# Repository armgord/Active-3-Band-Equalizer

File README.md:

# Electronic Circuit Design & Characterization Portfolio

[cite_start]A collection of high-performance analog and power electronics projects developed at **Tecnológico de Monterrey**[cite: 610, 612]. This repository documents the design, simulation, and physical implementation of fundamental electronic systems.

## 🚀 Projects Overview

### 1. Instrumentation Amplifier & Signal Conditioning
[cite_start]Designed a high-precision instrumentation amplifier using the **TL084 OpAmp**[cite: 787, 798]. 
* [cite_start]**Key Feature:** Achieved effective rejection of a 1V common-mode offset, outputting only the amplified differential signal[cite: 782, 783, 844].
* [cite_start]**Applications:** Sensor data acquisition and small-signal conditioning[cite: 783, 863].

### 2. Audio Power Amplifier (Push-Pull)
[cite_start]Developed a "Mono" audio amplifier combining an inverting OpAmp stage for gain control with a **TIP41C/TIP42C complementary push-pull stage**[cite: 978, 1012].
* [cite_start]**Performance:** Capable of driving an 8Ω speaker with high current (up to 6A) and minimal harmonic distortion[cite: 980, 1013, 1065].

### 3. Adjustable Voltage Regulator (1V - 12V)
[cite_start]Implemented a series linear regulator using an **LM358 OpAmp**, a Zener diode reference, and a **TIP31C power transistor**[cite: 869, 873].
* [cite_start]**Specs:** Adjustable output from 0.1V up to 12.3V with high-current stability (up to 300mA)[cite: 873, 943, 949, 957].

### 4. Signal Generation & PWM Motor Control
* [cite_start]**Waveform Generator:** Designed an oscillator for simultaneous square and triangular wave generation[cite: 1069, 1074].
* [cite_start]**DC Motor Control:** Implemented a speed control system using an **NE555 timer** for Pulse Width Modulation (PWM) to drive a DC motor via a chopper converter[cite: 1132, 1133, 1146].

## 📊 Characterization & Analysis
Each project includes detailed mathematical modeling and experimental verification:
* [cite_start]**Frequency Analysis:** Bode plots for Integrator/Differentiator circuits[cite: 752, 774].
* [cite_start]**Thermal Modeling:** Calculated heat sink requirements ($R_{\theta}$ ≈ 22.83°C/W) for power transistors[cite: 1017].
* [cite_start]**Efficiency:** Evaluation of power dissipation and conversion efficiency in linear vs. switching topologies[cite: 935, 936].

## 🛠️ Tools Used
* [cite_start]**Hardware:** Oscilloscopes (Keysight InfiniVision), Multimeters, Function Generators[cite: 623, 637, 641, 648].
* [cite_start]**Components:** TL084, LM358, NE555, TIP31C/41C/42C[cite: 787, 869, 1012, 1146].

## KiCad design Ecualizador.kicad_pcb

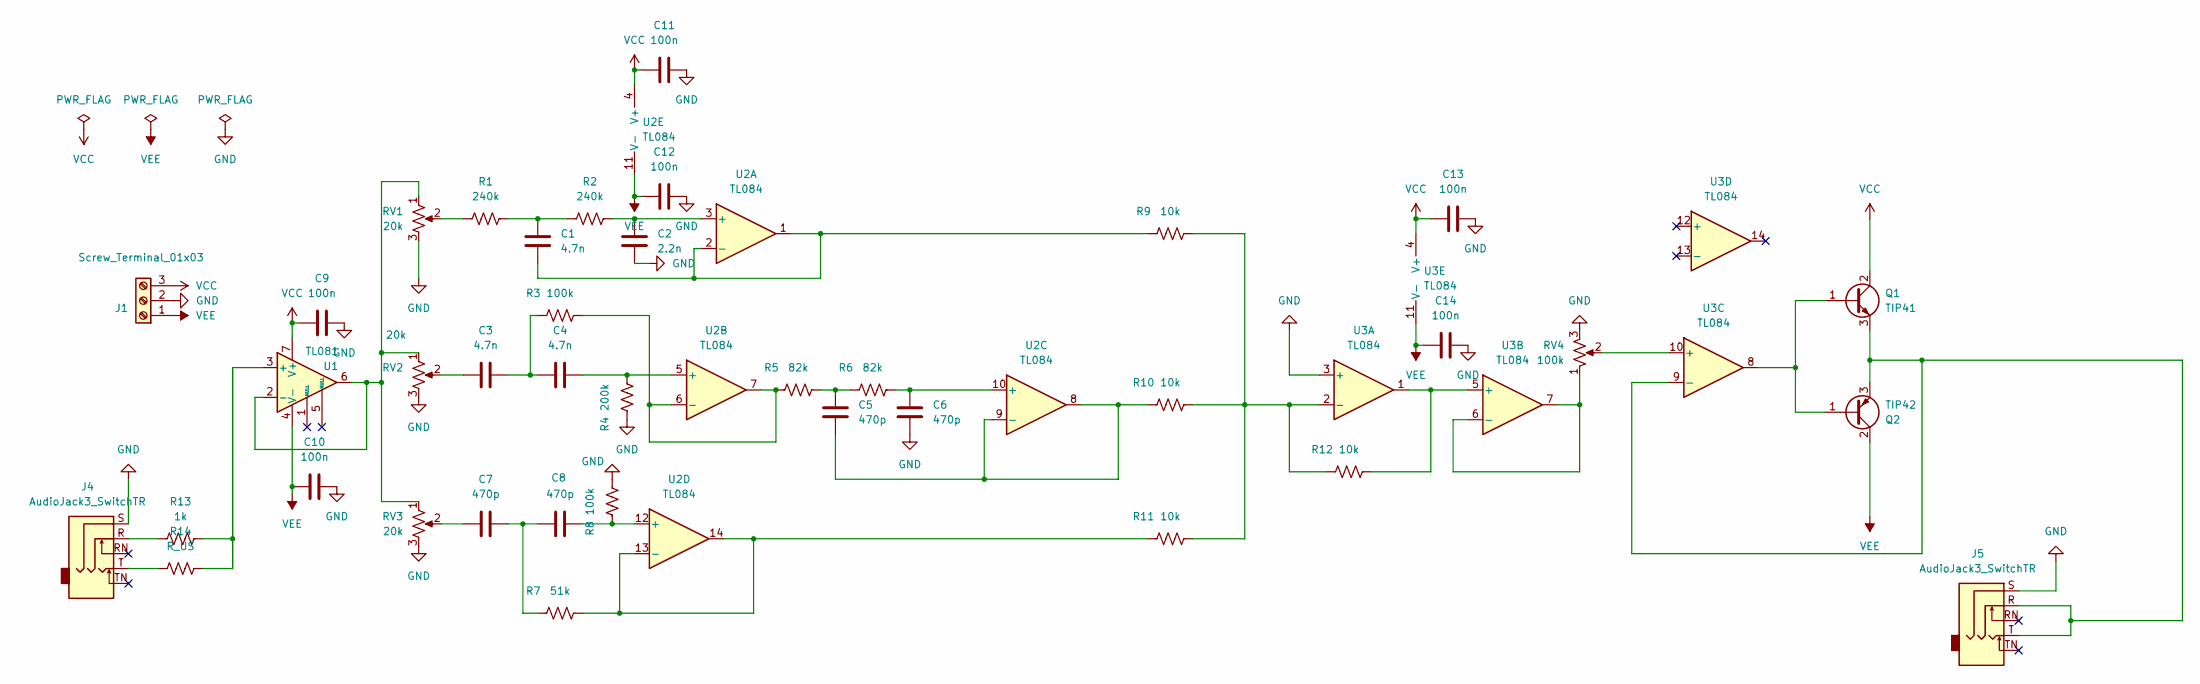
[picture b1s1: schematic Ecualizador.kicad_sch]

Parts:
C1, C3, C4: 4.7n; C_Axial_L3.8mm_D2.6mm_P7.50mm_Horizontal
C2: 2.2n; C_Axial_L3.8mm_D2.6mm_P7.50mm_Horizontal
C5, C6, C7, C8: 470p; C_Axial_L3.8mm_D2.6mm_P7.50mm_Horizontal
C9, C10, C11, C12, C13, C14: 100n; C_Axial_L3.8mm_D2.6mm_P7.50mm_Horizontal
J1: Screw_Terminal_01x03; TerminalBlock_Phoenix_MPT-0,5-3-2.54_1x03_P2.54mm_Horizontal
J4, J5: AudioJack3_SwitchTR; Jack_3.5mm_CUI_SJ-3523-SMT_Horizontal
Q1: TIP41; TO-220-3_Vertical
Q2: TIP42; TO-220-3_Vertical
R1, R2: 240k; R_Axial_DIN0204_L3.6mm_D1.6mm_P5.08mm_Horizontal
R3, R8: 100k; R_Axial_DIN0204_L3.6mm_D1.6mm_P5.08mm_Horizontal
R4: 200k; R_Axial_DIN0204_L3.6mm_D1.6mm_P5.08mm_Horizontal
R5, R6: 82k; R_Axial_DIN0204_L3.6mm_D1.6mm_P5.08mm_Horizontal
R7: 51k; R_Axial_DIN0204_L3.6mm_D1.6mm_P5.08mm_Horizontal
R9, R10, R11, R12: 10k; R_Axial_DIN0204_L3.6mm_D1.6mm_P5.08mm_Horizontal
R13: 1k; R_Axial_DIN0204_L3.6mm_D1.6mm_P5.08mm_Horizontal
R14: R_US; R_Axial_DIN0204_L3.6mm_D1.6mm_P5.08mm_Horizontal
RV1, RV2, RV3: 20k; Potentiometer_Alps_RK163_Single_Horizontal
RV4: 100k; Potentiometer_Alps_RK163_Single_Horizontal
U1: TL081; DIP-8_W7.62mm
U2, U3: TL084; DIP-14_W7.62mm

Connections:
GND: C2.1, C6.1, C9.2, C10.2, C11.2, C12.2, C13.2, C14.2, J1.2, J4.S, J5.S, R4.1, R8.2, RV1.3, RV2.3, RV3.3, RV4.3, U3.3 (+)
unnamed: C1.2, R1.2, R2.1
unnamed: C3.1, C4.2, R3.1
unnamed: C3.2, RV2.2
unnamed: C5.2, R5.2, R6.1
unnamed: C7.1, C8.2, R7.1
unnamed: C7.2, RV3.2
unnamed: J4.R, R13.1
unnamed: J4.T, R14.1
unnamed: Q1.1 (B), Q2.1 (B), U3.8
unnamed: J5.R, J5.T, Q1.3 (E), Q2.3 (E), U3.9 (-)
unnamed: R1.1, RV1.2
unnamed: R13.2, R14.2, U1.3 (+)
unnamed: RV1.1, RV2.1, RV3.1, U1.2 (-), U1.6
unnamed: C2.2, R2.2, U2.3 (+)
unnamed: C1.1, R9.1, U2.1, U2.2 (-)
unnamed: C4.1, R4.2, U2.5 (+)
unnamed: R3.2, R5.1, U2.6 (-), U2.7
unnamed: C6.2, R6.2, U2.10 (+)
unnamed: C5.1, R10.1, U2.8, U2.9 (-)
unnamed: C8.1, R8.1, U2.12 (+)
unnamed: R7.2, R11.1, U2.13 (-), U2.14
unnamed: R9.2, R10.2, R11.2, R12.1, U3.2 (-)
unnamed: R12.2, U3.1, U3.5 (+)
unnamed: RV4.1, U3.6 (-), U3.7
unnamed: RV4.2, U3.10 (+)
VCC: C9.1, C11.1, C13.1, J1.3, Q1.2 (C), U1.7 (V+), U2.4 (V+), U3.4 (V+)
VEE: C10.1, C12.1, C14.1, J1.1, Q2.2 (C), U1.4 (V-), U2.11 (V-), U3.11 (V-)

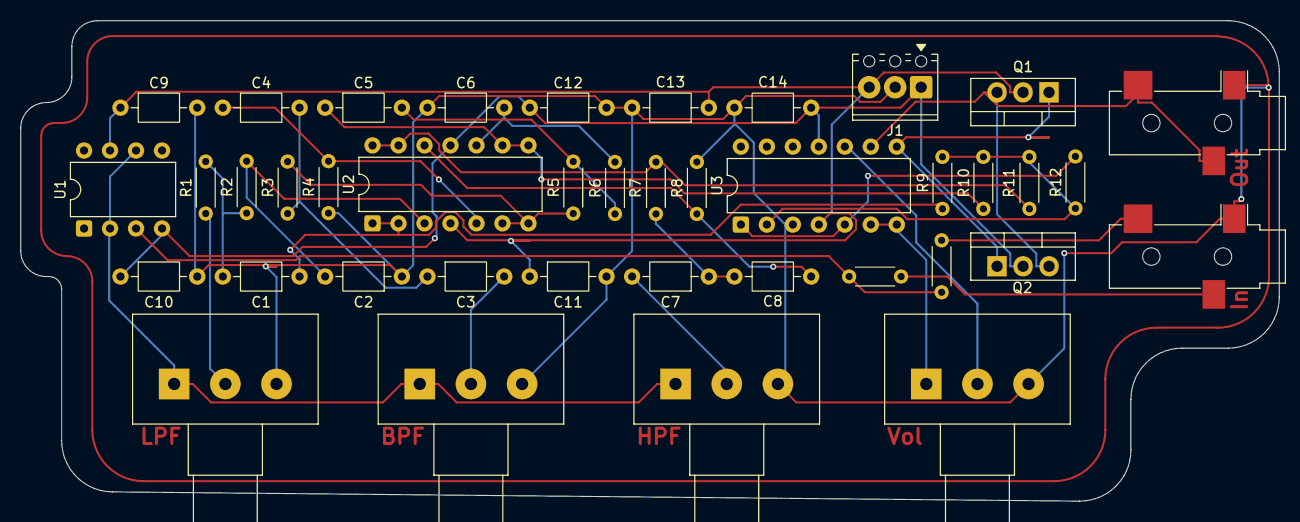
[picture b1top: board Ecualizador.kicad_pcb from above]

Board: 2 copper layers, 123.0 x 47.0 mm, 40 parts (0 on the bottom side), 28 nets.

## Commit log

2026-02-12 Add README for electronic circuit design portfolio
    Added a comprehensive README detailing electronic circuit design projects, including instrumentation amplifiers, audio power amplifiers, voltage regulators, and signal generation systems.
2026-02-12 Delete content from README.md
    Removed the entire content of the README.md file, which included project descriptions and details about electronic circuit design and characterization.
